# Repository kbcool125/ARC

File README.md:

# ARC
Code, documentation and other items relavent to the Aberystwyth Robotics Club

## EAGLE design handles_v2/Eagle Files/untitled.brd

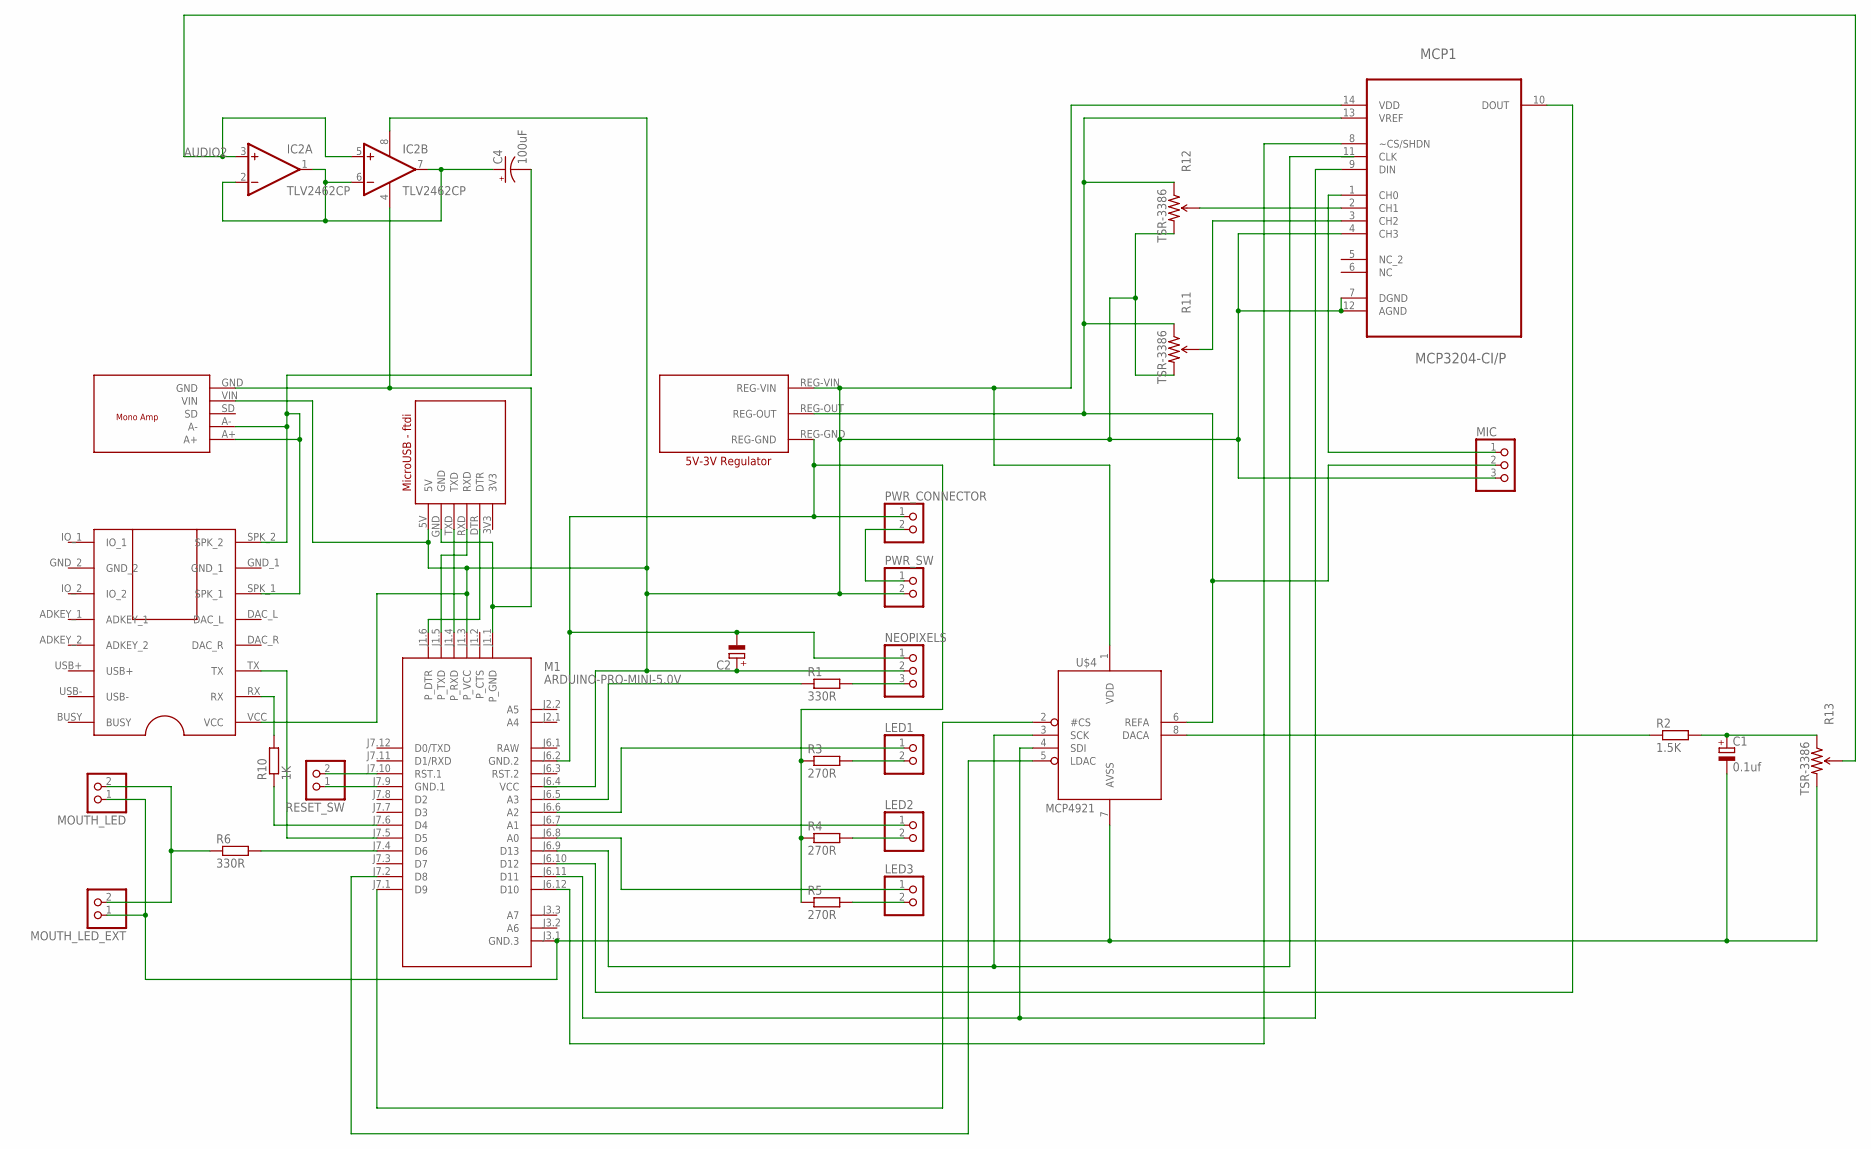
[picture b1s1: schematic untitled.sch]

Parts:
C1: 0.1uf; E2,5-6E
C2: CPOL-EUE2,5-6E; E2,5-6E
C4: 100uF; CPOL-RADIAL-100UF-25V
IC2: TLV2462CP; DIL08
LED1, LED2, LED3: PINHD-1X2; 1X02
M1: ARDUINO-PRO-MINI-5.0V; ARDUINO-PRO-MINI
MCP1: MCP3204-CI/P; DIP254P762X432-14
MIC: PINHD-1X3; 1X03
MOUTH_LED: PINHD-1X2; 1X02
MOUTH_LED_EXT: PINHD-1X2; 1X02
NEOPIXELS: PINHD-1X3; 1X03
PWR_CONNECTOR: PINHD-1X2; 1X02
PWR_SW: PINHD-1X2; 1X02
R1, R6: 330R; 0207/7
R2: 1.5K; 0207/7
R3, R4, R5: 270R; 0207/7
R10: 1K; 0207/7
R11, R12, R13: TSR-3386; 3386U
RESET_SW: PINHD-1X2; 1X02
U$1: DPLAYER-MINI-DEV; DPLAYER-MINI-PAC
U$2: MICRO-USB-DEV; MICRO-USB-PAC
U$4: MCP4921; DIL08
U$5: 5V-TO-3V-REG-DEV; 5V-TO-3V-REG-PAC
U$6: MONO-AMP-DEV; MONO-AMP-PAC

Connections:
3V3: U$2.3V3
AUDIO2: IC2.3 (+IN), IC2.5 (+IN), R13.2 (WIPER)
AVSS: C1.-, M1.J3.1 (GND.3), MOUTH_LED.1, MOUTH_LED_EXT.1, R13.3 (CW), U$4.7 (AVSS)
GND_1: IC2.4 (V-), M1.J1.1 (P_GND), U$1.GND_1, U$2.GND, U$6.GND
GND_2: U$1.GND_2
unnamed: NEOPIXELS.3, R1.2
unnamed: M1.J1.4 (P_RXD), U$2.TXD
unnamed: M1.J1.5 (P_TXD), U$2.RXD
unnamed: M1.J1.6 (P_DTR), U$2.DTR
unnamed: LED3.1, M1.J6.8 (A0)
unnamed: LED1.2, R3.2
unnamed: LED2.2, R4.2
unnamed: C4.2 (-), U$1.SPK_1, U$1.SPK_2, U$6.A+, U$6.A-
unnamed: LED1.1, M1.J6.6 (A2)
unnamed: MCP1.2 (CH1), R12.2 (WIPER)
unnamed: PWR_CONNECTOR.2, PWR_SW.1
unnamed: M1.J7.5 (D5), U$1.TX
unnamed: LED2.1, M1.J6.7 (A1)
unnamed: R10.2, U$1.RX
unnamed: LED3.2, R5.2
unnamed: M1.J7.6 (D4), R10.1
unnamed: C2.-, M1.J6.2 (GND.2), NEOPIXELS.1, PWR_CONNECTOR.1, R3.1, R4.1, R5.1, U$5.REG-GND
unnamed: MCP1.13 (VREF), MIC.2, R11.1 (CCW), R12.1 (CCW), U$4.6 (REFA), U$5.REG-OUT
unnamed: M1.J6.5 (A3), R1.1
unnamed: M1.J7.10 (RST.1), RESET_SW.2
unnamed: M1.J7.9 (GND.1), RESET_SW.1
unnamed: C4.1 (+), IC2.1 (OUT), IC2.2 (-IN), IC2.6 (-IN), IC2.7 (OUT)
unnamed: MCP1.3 (CH2), R11.2 (WIPER)
unnamed: M1.J6.9 (D13), U$4.3 (SCK)
unnamed: M1.J6.10 (D12), MCP1.10 (DOUT)
unnamed: M1.J6.12 (D10), MCP1.8 (~CS/SHDN)
unnamed: M1.J6.11 (D11), MCP1.9 (DIN), U$4.4 (SDI)
unnamed: MCP1.1 (CH0), MIC.1
unnamed: C1.+, R2.2, R13.1 (CCW)
unnamed: M1.J7.4 (D6), R6.2
unnamed: R2.1, U$4.8 (DACA)
unnamed: MOUTH_LED.2, MOUTH_LED_EXT.2, R6.1
unnamed: M1.J7.1 (D9), U$4.2 (#CS)
unnamed: M1.J7.2 (D8), U$4.5 (LDAC)
RAW: M1.J6.1 (RAW)
VCC: M1.J6.4 (VCC)
VDD: C2.+, IC2.8 (V+), M1.J1.3 (P_VCC), MCP1.4 (CH3), MCP1.7 (DGND), MCP1.12 (AGND), MCP1.14 (VDD), MIC.3, NEOPIXELS.2, PWR_SW.2, R11.3 (CW), R12.3 (CW), U$1.VCC, U$2.5V, U$4.1 (VDD), U$5.REG-VIN, U$6.VIN

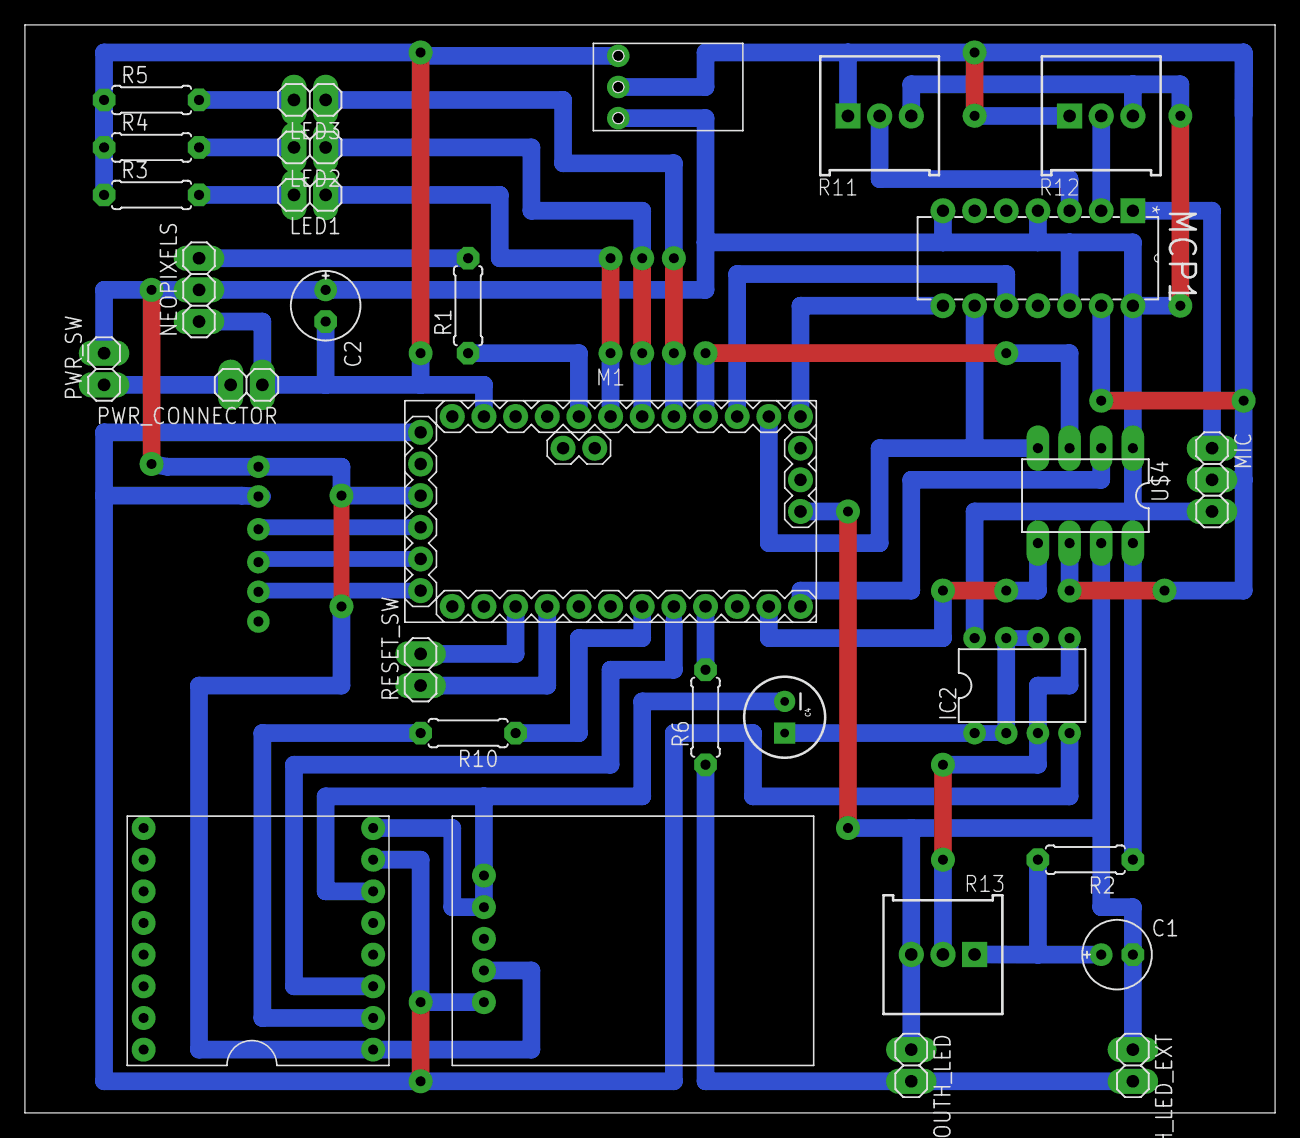
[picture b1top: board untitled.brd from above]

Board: 2 copper layers, 100.3 x 87.3 mm, 31 parts (1 on the bottom side), 38 nets.

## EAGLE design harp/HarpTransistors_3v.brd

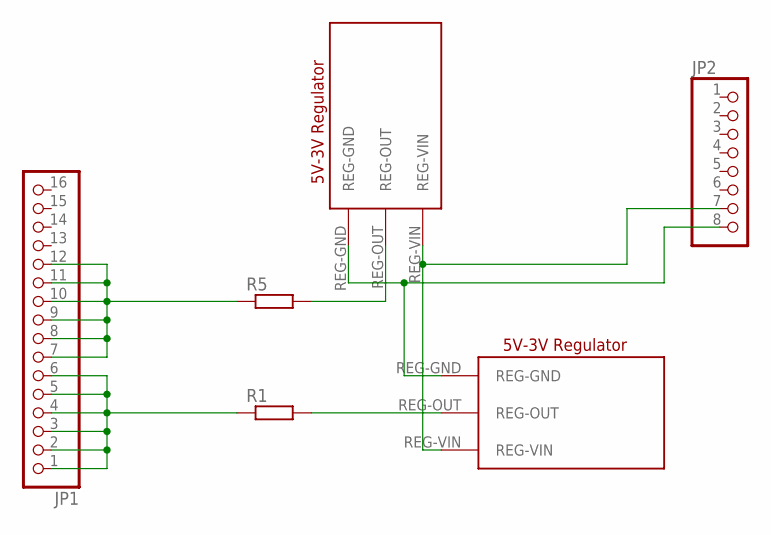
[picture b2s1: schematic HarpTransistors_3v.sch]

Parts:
JP1: PINHD-1X16; 1X16
JP2: PINHD-1X8; 1X08
R1, R5: R-EU_0204/5; 0204/5
U$1, U$2: 5V-TO-3V-REG-DEV; 5V-TO-3V-REG-PAC

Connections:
unnamed: R5.2, U$1.REG-OUT
unnamed: JP1.1, JP1.2, JP1.3, JP1.4, JP1.5, JP1.6, R1.1
unnamed: R1.2, U$2.REG-OUT
unnamed: JP2.8, U$1.REG-GND, U$2.REG-GND
unnamed: JP2.7, U$1.REG-VIN, U$2.REG-VIN
unnamed: JP1.7, JP1.8, JP1.9, JP1.10, JP1.11, JP1.12, R5.1

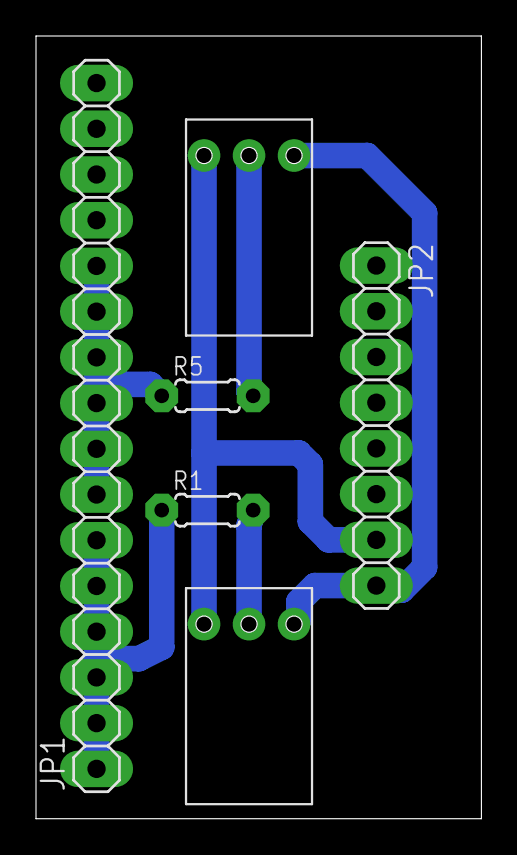
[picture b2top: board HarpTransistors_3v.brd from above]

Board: 2 copper layers, 24.7 x 43.5 mm, 6 parts (0 on the bottom side), 6 nets.

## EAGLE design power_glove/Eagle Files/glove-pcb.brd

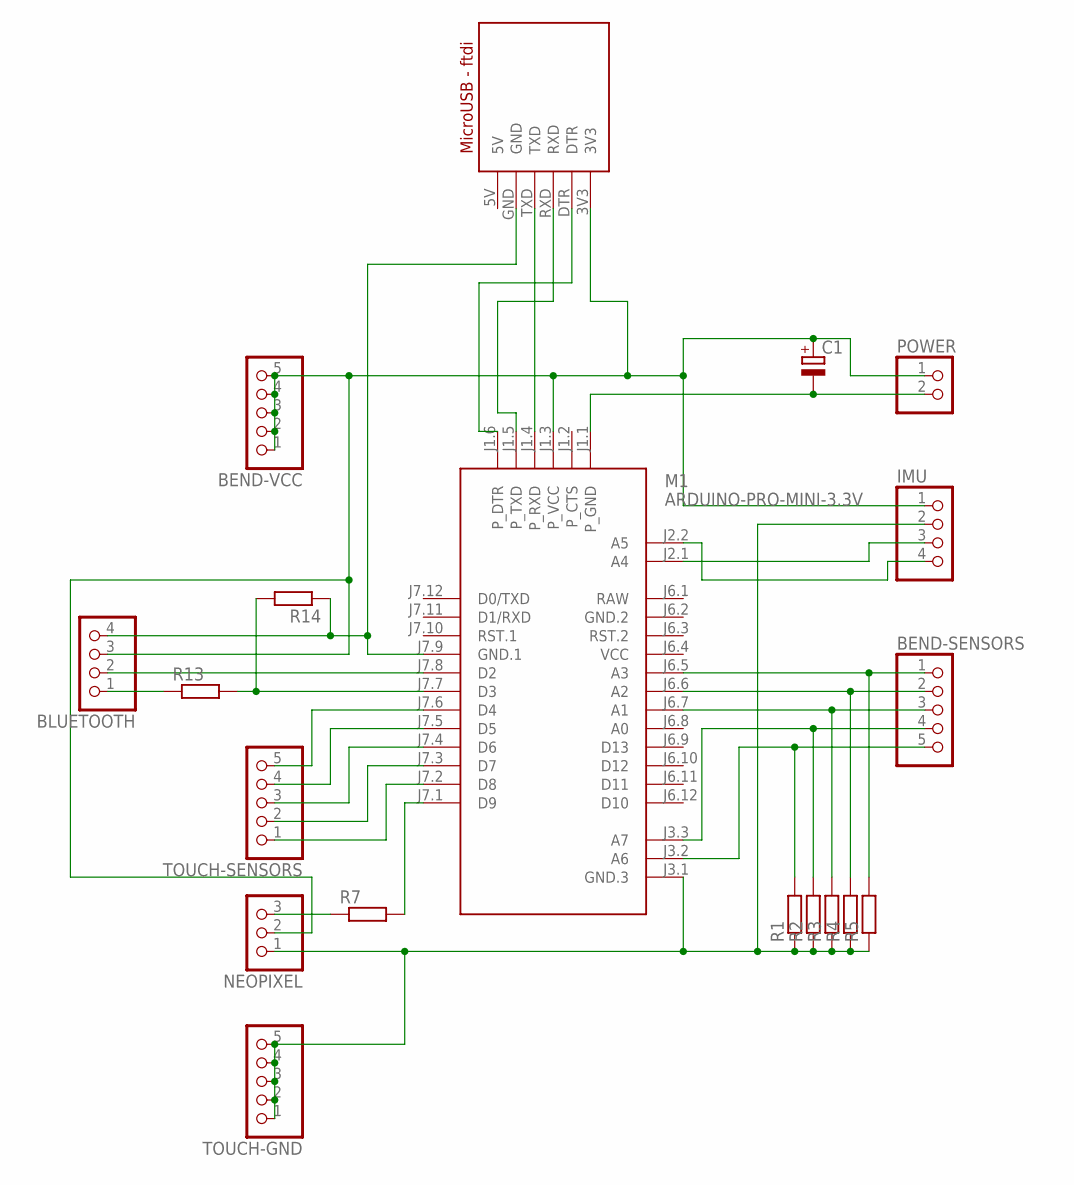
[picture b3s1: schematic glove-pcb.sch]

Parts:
BEND-SENSORS: PINHD-1X5; 1X05
BEND-VCC: PINHD-1X5; 1X05
BLUETOOTH: PINHD-1X4; 1X04
C1: CPOL-EUE2-5; E2-5
IMU: PINHD-1X4; 1X04
M1: ARDUINO-PRO-MINI-3.3V; ARDUINO-PRO-MINI
NEOPIXEL: PINHD-1X3; 1X03
POWER: PINHD-1X2; 1X02
R1, R2, R3, R4, R5: R-EU_0204/7; 0204/7
R7, R13, R14: R-EU_0204/2V; 0204V
TOUCH-GND: PINHD-1X5; 1X05
TOUCH-SENSORS: PINHD-1X5; 1X05
U$1: MICRO-USB-DEV; MICRO-USB-PAC

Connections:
5V: U$1.5V
GND.2: M1.J6.2 (GND.2)
unnamed: NEOPIXEL.3, R7.1
unnamed: IMU.3, M1.J2.1 (A4)
unnamed: M1.J7.1 (D9), R7.2
unnamed: IMU.4, M1.J2.2 (A5)
unnamed: M1.J1.4 (P_RXD), U$1.TXD
unnamed: M1.J1.5 (P_TXD), U$1.RXD
unnamed: BLUETOOTH.1, R13.1
unnamed: BLUETOOTH.2, M1.J7.8 (D2)
unnamed: BEND-SENSORS.1, M1.J6.5 (A3), R5.2
unnamed: BLUETOOTH.4, M1.J7.9 (GND.1), R14.1, U$1.GND
unnamed: IMU.2, M1.J3.1 (GND.3), NEOPIXEL.1, R1.1, R2.1, R3.1, R4.1, R5.1, TOUCH-GND.1, TOUCH-GND.2, TOUCH-GND.3, TOUCH-GND.4, TOUCH-GND.5
unnamed: M1.J7.2 (D8), TOUCH-SENSORS.1
unnamed: M1.J7.3 (D7), TOUCH-SENSORS.2
unnamed: C1.-, M1.J1.1 (P_GND), POWER.2
unnamed: M1.J7.4 (D6), TOUCH-SENSORS.3
unnamed: M1.J7.5 (D5), TOUCH-SENSORS.4
unnamed: M1.J7.6 (D4), TOUCH-SENSORS.5
unnamed: BEND-SENSORS.2, M1.J6.6 (A2), R4.2
unnamed: BEND-SENSORS.3, M1.J6.7 (A1), R3.2
unnamed: BEND-SENSORS.4, M1.J3.3 (A7), R2.2
unnamed: BEND-SENSORS.5, M1.J3.2 (A6), R1.2
unnamed: M1.J7.7 (D3), R13.2, R14.2
unnamed: M1.J1.6 (P_DTR), U$1.DTR
unnamed: BEND-VCC.1, BEND-VCC.2, BEND-VCC.3, BEND-VCC.4, BEND-VCC.5, BLUETOOTH.3, C1.+, IMU.1, M1.J1.3 (P_VCC), NEOPIXEL.2, POWER.1, U$1.3V3
RAW: M1.J6.1 (RAW)
VCC: M1.J6.4 (VCC)

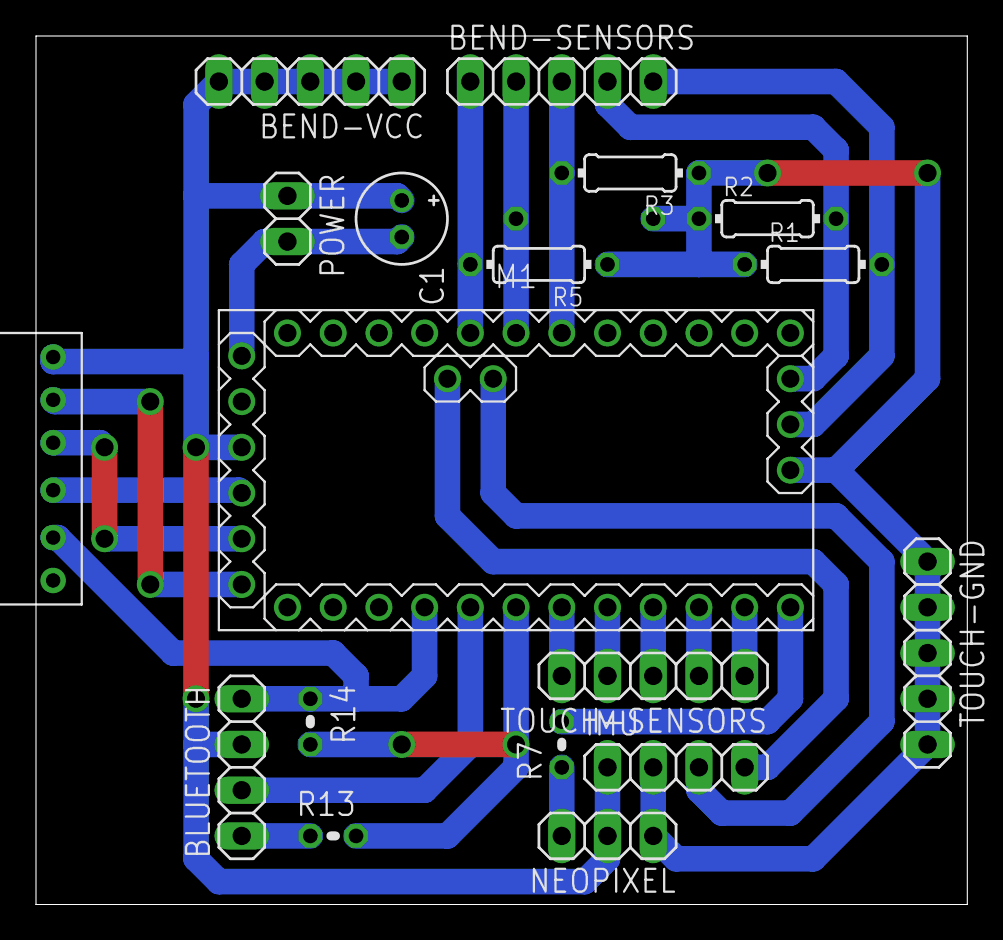
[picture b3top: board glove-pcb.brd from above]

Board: 2 copper layers, 51.7 x 48.2 mm, 19 parts (1 on the bottom side), 24 nets.

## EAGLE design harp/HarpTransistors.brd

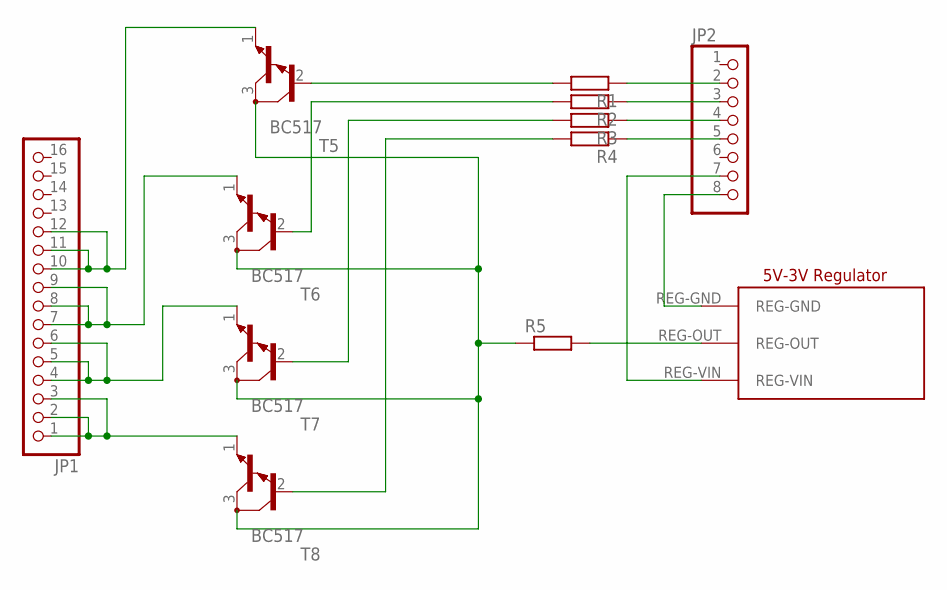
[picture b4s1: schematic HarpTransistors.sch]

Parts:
JP1: PINHD-1X16; 1X16
JP2: PINHD-1X8; 1X08
R1, R2, R3, R4, R5: R-EU_0204/5; 0204/5
T5, T6, T7, T8: BC517; TO92
U$1: 5V-TO-3V-REG-DEV; 5V-TO-3V-REG-PAC

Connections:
unnamed: R1.2, T5.2 (B)
unnamed: JP2.5, R4.1
unnamed: JP2.4, R3.1
unnamed: JP2.3, R2.1
unnamed: JP2.2, R1.1
unnamed: R4.2, T8.2 (B)
unnamed: R2.2, T6.2 (B)
unnamed: JP2.8, U$1.REG-GND
unnamed: JP1.4, JP1.5, JP1.6, T7.1 (E)
unnamed: JP1.7, JP1.8, JP1.9, T6.1 (E)
unnamed: JP1.10, JP1.11, JP1.12, T5.1 (E)
unnamed: R5.1, T5.3 (C), T6.3 (C), T7.3 (C), T8.3 (C)
unnamed: JP1.1, JP1.2, JP1.3, T8.1 (E)
unnamed: R3.2, T7.2 (B)
unnamed: JP2.7, U$1.REG-VIN
unnamed: R5.2, U$1.REG-OUT

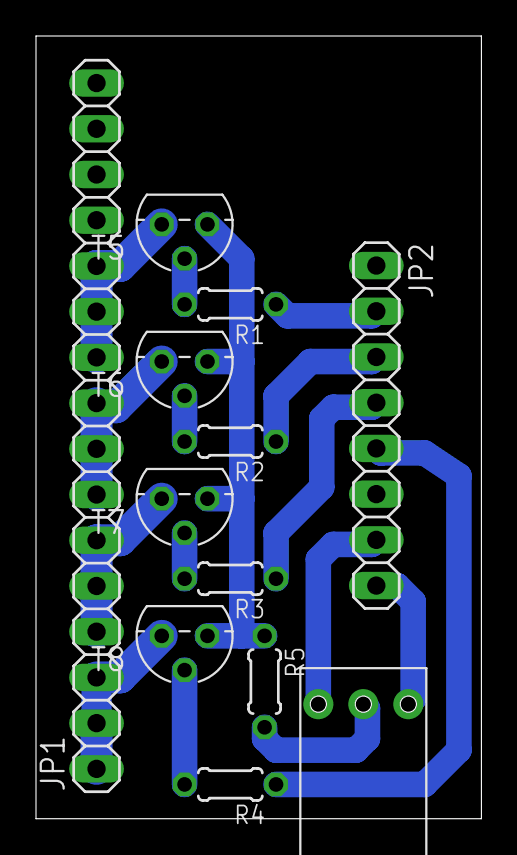
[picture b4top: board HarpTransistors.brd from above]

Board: 2 copper layers, 24.7 x 43.5 mm, 12 parts (0 on the bottom side), 16 nets.

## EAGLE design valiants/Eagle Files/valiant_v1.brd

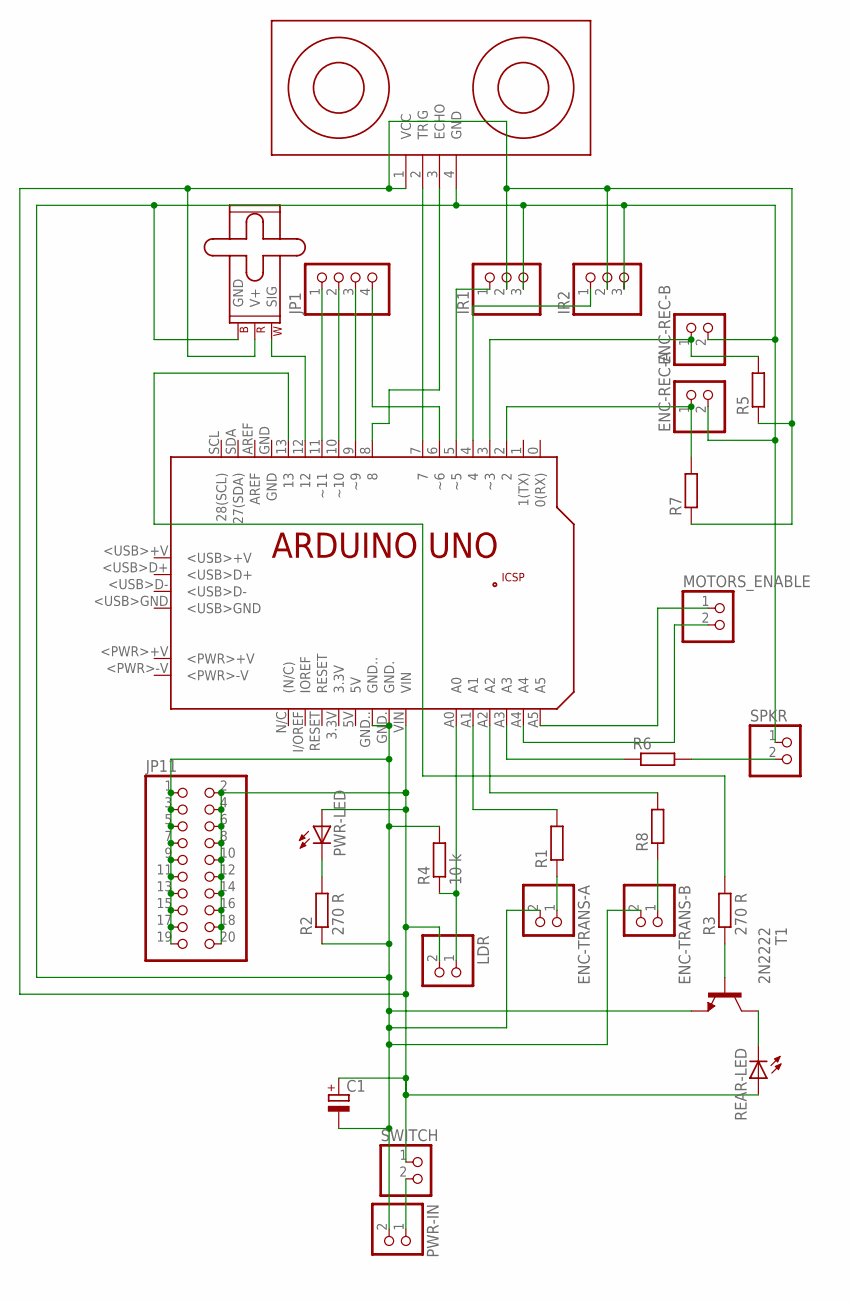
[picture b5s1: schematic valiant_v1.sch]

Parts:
C1: CPOL-EUE2,5-6E; E2,5-6E
ENC-REC-A: PINHD-1X2; 1X02
ENC-REC-B: PINHD-1X2; 1X02
ENC-TRANS-A: PINHD-1X2; 1X02
ENC-TRANS-B: PINHD-1X2; 1X02
IR1, IR2: PINHD-1X3; 1X03
JP1: PINHD-1X4; 1X04
JP11: PINHD-2X10; 2X10
LDR: PINHD-1X2; 1X02
M1: SMALL_SERVO; 1X03
MOTORS_ENABLE: PINHD-1X2; 1X02
PCB1: ARDUINO_UNO
PWR-IN: PINHD-1X2; 1X02
PWR-LED: LED5MM
R1, R5, R6, R7, R8: R-EU_0204/7; 0204/7
R2, R3: 270 R; 0204/7
R4: 10 k; 0204/7
REAR-LED: LED5MM
SPKR: PINHD-1X2; 1X02
SWITCH: PINHD-1X2; 1X02
T1: 2N2222; TO92-EBC-OVAL
U$1: ULTRASONIC-HC-SR04#V

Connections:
unnamed: R3.1, T1.B
unnamed: PCB1.7, U$1.2 (TRIG)
unnamed: JP1.4, PCB1.6 (~6)
unnamed: JP1.3, PCB1.9 (~9)
unnamed: JP1.2, PCB1.10 (~10)
unnamed: JP1.1, PCB1.11 (~11)
unnamed: PCB1.8, U$1.3 (ECHO)
unnamed: ENC-TRANS-A.1, R1.1
unnamed: LDR.1, PCB1.A0, R4.1
unnamed: PCB1.A1, R1.2
unnamed: PCB1.A2, R8.2
unnamed: PCB1.13, R3.2
unnamed: ENC-REC-A.1, PCB1.2, R7.2
unnamed: C1.+, IR1.2, IR2.2, JP11.2, JP11.4, JP11.6, JP11.8, JP11.10, JP11.12, JP11.14, JP11.16, JP11.18, JP11.20, LDR.2, M1.2 (V+), PCB1.VIN, PWR-LED.A, R5.1, R7.1, REAR-LED.A, SWITCH.1, U$1.1 (VCC)
unnamed: PWR-IN.1, SWITCH.2
unnamed: ENC-TRANS-B.1, R8.1
unnamed: PWR-LED.K (C), R2.2
unnamed: M1.1 (SIG), PCB1.12
unnamed: REAR-LED.K (C), T1.C
unnamed: MOTORS_ENABLE.2, PCB1.A4
unnamed: IR1.1, PCB1.5 (~5)
unnamed: IR2.1, PCB1.4
unnamed: ENC-REC-B.1, PCB1.3 (~3), R5.2
unnamed: R6.2, SPKR.2
unnamed: PCB1.A3, R6.1
unnamed: C1.-, ENC-REC-A.2, ENC-REC-B.2, ENC-TRANS-A.2, ENC-TRANS-B.2, IR1.3, IR2.3, JP11.1, JP11.3, JP11.5, JP11.7, JP11.9, JP11.11, JP11.13, JP11.15, JP11.17, JP11.19, M1.3 (GND), PCB1.GND., PCB1.GND.., PWR-IN.2, R2.1, R4.2, SPKR.1, T1.E, U$1.4 (GND)
unnamed: MOTORS_ENABLE.1, PCB1.A5

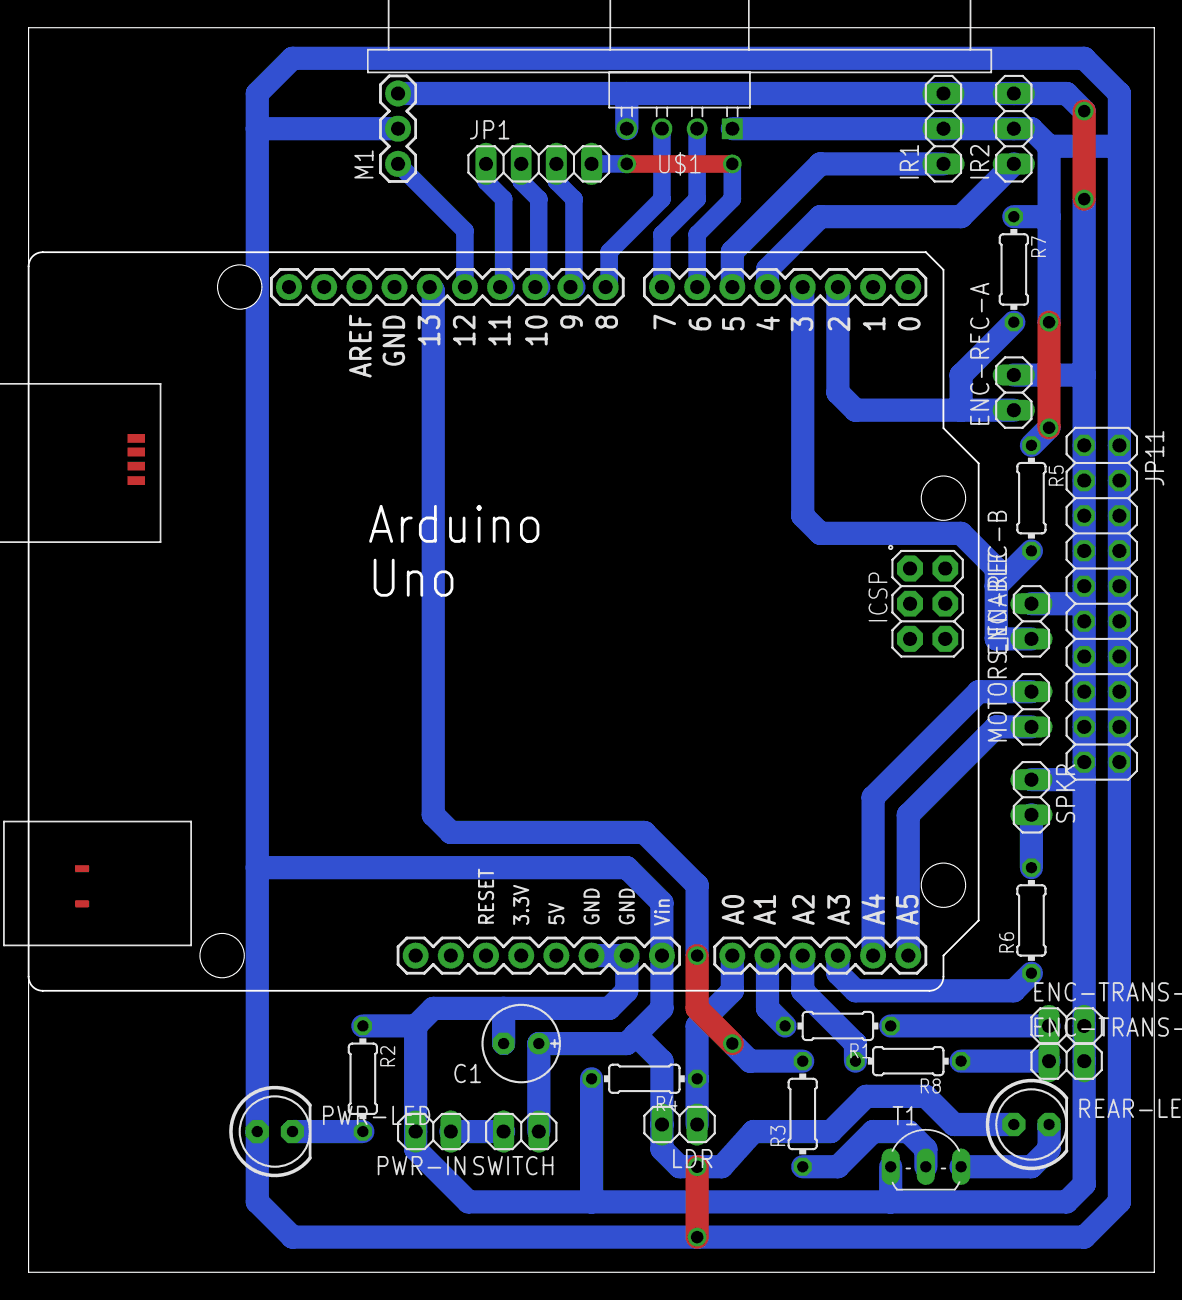
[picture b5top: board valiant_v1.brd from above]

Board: 2 copper layers, 81.3 x 89.8 mm, 28 parts (0 on the bottom side), 27 nets.

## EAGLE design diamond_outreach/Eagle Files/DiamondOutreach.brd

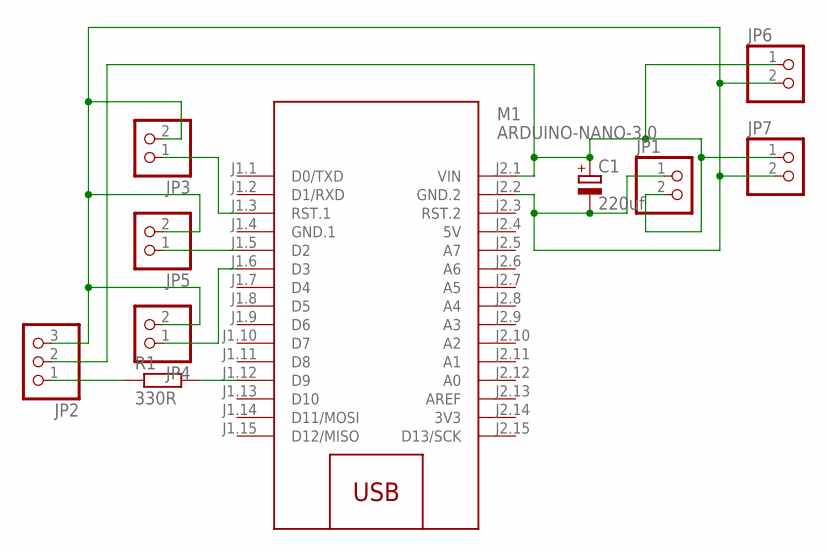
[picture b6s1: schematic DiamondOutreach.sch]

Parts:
C1: 220uf; E2,5-6E
JP1, JP3, JP4, JP5, JP6, JP7: PINHD-1X2; 1X02
JP2: PINHD-1X3; 1X03
M1: ARDUINO-NANO-3.0
R1: 330R; 0204/7

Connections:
3V3: M1.J2.14 (3V3)
5V: M1.J2.4 (5V)
GND.1: M1.J1.4 (GND.1)
unnamed: M1.J1.12 (D9), R1.2
unnamed: JP2.1, R1.1
unnamed: JP3.1, M1.J1.3 (RST.1)
unnamed: C1.+, JP1.2, JP2.2, JP6.1, JP7.1, M1.J2.1 (VIN)
unnamed: JP4.1, M1.J1.6 (D3)
unnamed: JP5.1, M1.J1.5 (D2)
unnamed: C1.-, JP1.1, JP2.3, JP3.2, JP4.2, JP5.2, JP6.2, JP7.2, M1.J2.2 (GND.2)

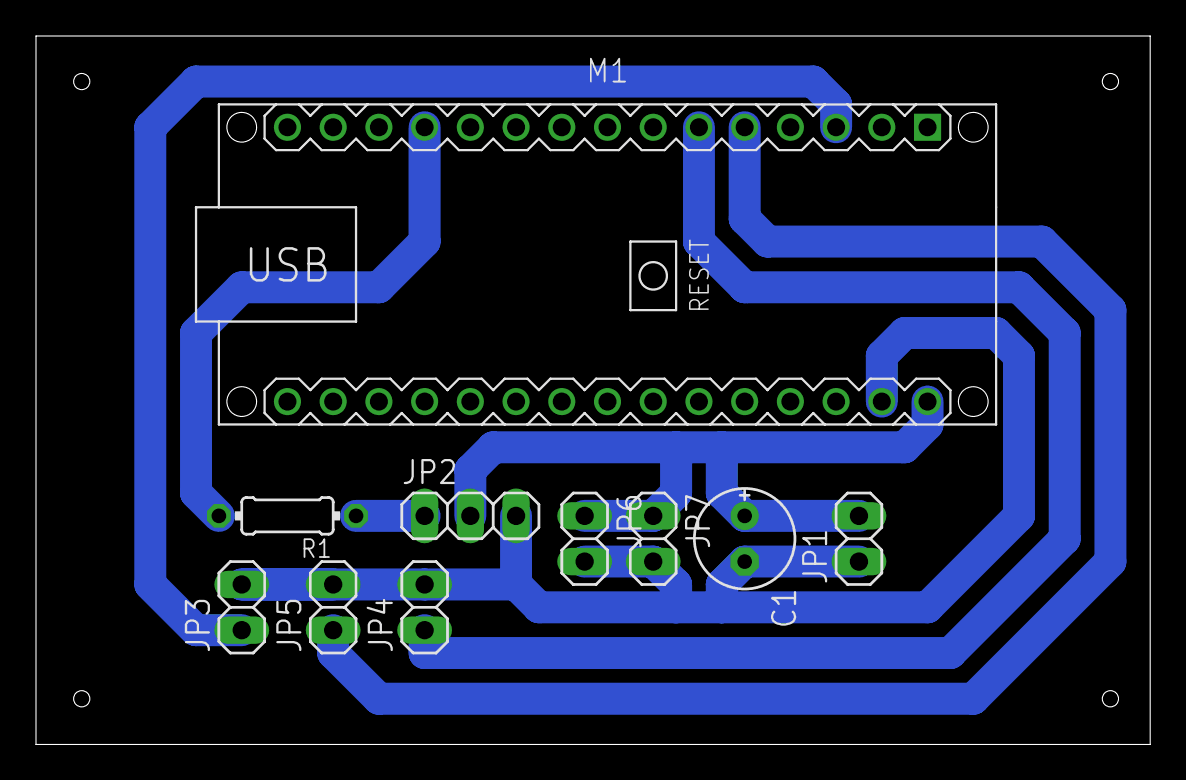
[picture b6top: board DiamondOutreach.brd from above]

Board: 2 copper layers, 61.9 x 39.4 mm, 10 parts (0 on the bottom side), 7 nets.

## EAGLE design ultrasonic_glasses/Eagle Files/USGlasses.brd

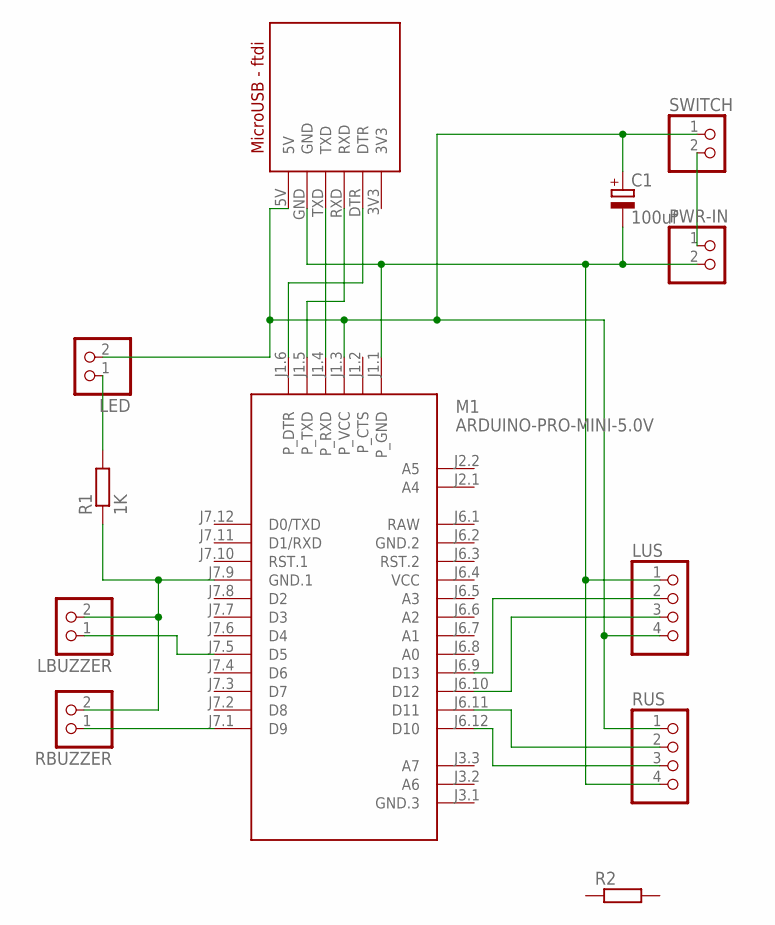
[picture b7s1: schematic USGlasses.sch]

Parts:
C1: 100uf; E2,5-6E
LBUZZER: PINHD-1X2; 1X02
LED: PINHD-1X2; 1X02
LUS: PINHD-1X4; 1X04
M1: ARDUINO-PRO-MINI-5.0V; ARDUINO-PRO-MINI
PWR-IN: PINHD-1X2; 1X02
R1: 1K; 0204/7
R2: R-EU_0204/7; 0204/7
RBUZZER: PINHD-1X2; 1X02
RUS: PINHD-1X4; 1X04
SWITCH: PINHD-1X2; 1X02
U$1: MICRO-USB-DEV; MICRO-USB-PAC

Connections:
3V3: U$1.3V3
GND.2: M1.J6.2 (GND.2)
unnamed: M1.J1.4 (P_RXD), U$1.TXD
unnamed: M1.J1.5 (P_TXD), U$1.RXD
unnamed: M1.J1.6 (P_DTR), U$1.DTR
unnamed: LED.1, R1.2
unnamed: LUS.3, M1.J6.10 (D12)
unnamed: PWR-IN.1, SWITCH.2
unnamed: C1.+, LED.2, LUS.4, M1.J1.3 (P_VCC), RUS.1, SWITCH.1, U$1.5V
unnamed: C1.-, LUS.1, M1.J1.1 (P_GND), PWR-IN.2, RUS.4, U$1.GND
unnamed: LUS.2, M1.J6.9 (D13)
unnamed: M1.J6.11 (D11), RUS.2
unnamed: M1.J6.12 (D10), RUS.3
unnamed: LBUZZER.2, M1.J7.9 (GND.1), R1.1, RBUZZER.2
unnamed: M1.J7.1 (D9), RBUZZER.1
unnamed: LBUZZER.1, M1.J7.5 (D5)
RAW: M1.J6.1 (RAW)
VCC: M1.J6.4 (VCC)

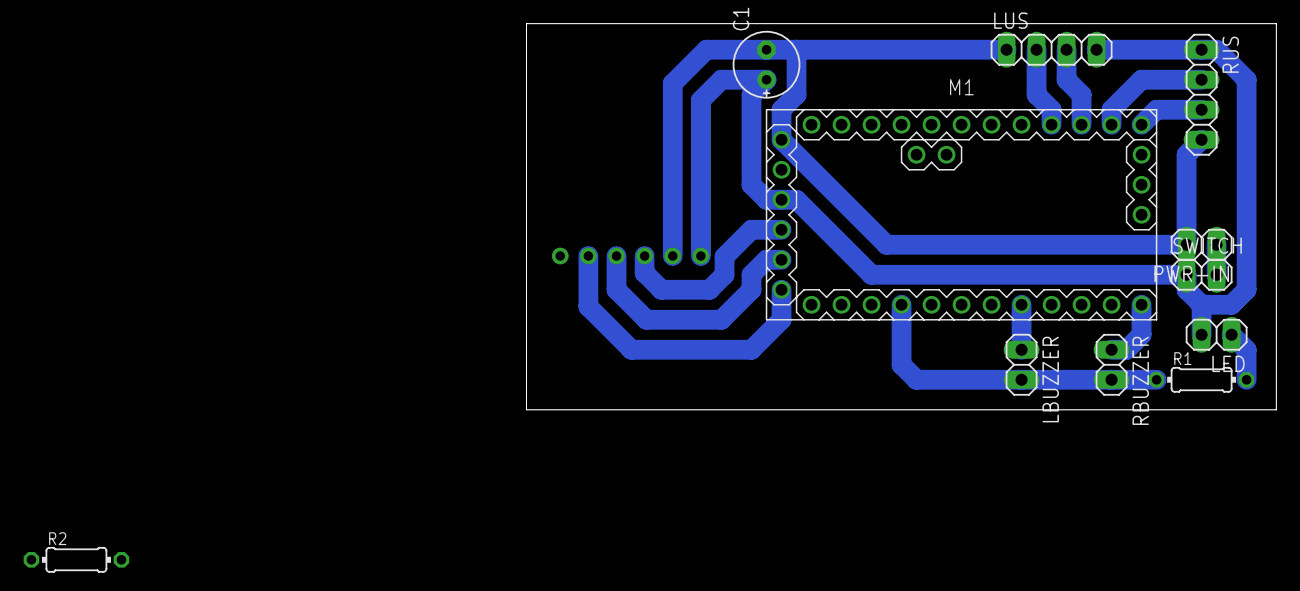
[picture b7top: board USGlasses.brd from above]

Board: 2 copper layers, 63.5 x 32.7 mm, 12 parts (1 on the bottom side), 14 nets.

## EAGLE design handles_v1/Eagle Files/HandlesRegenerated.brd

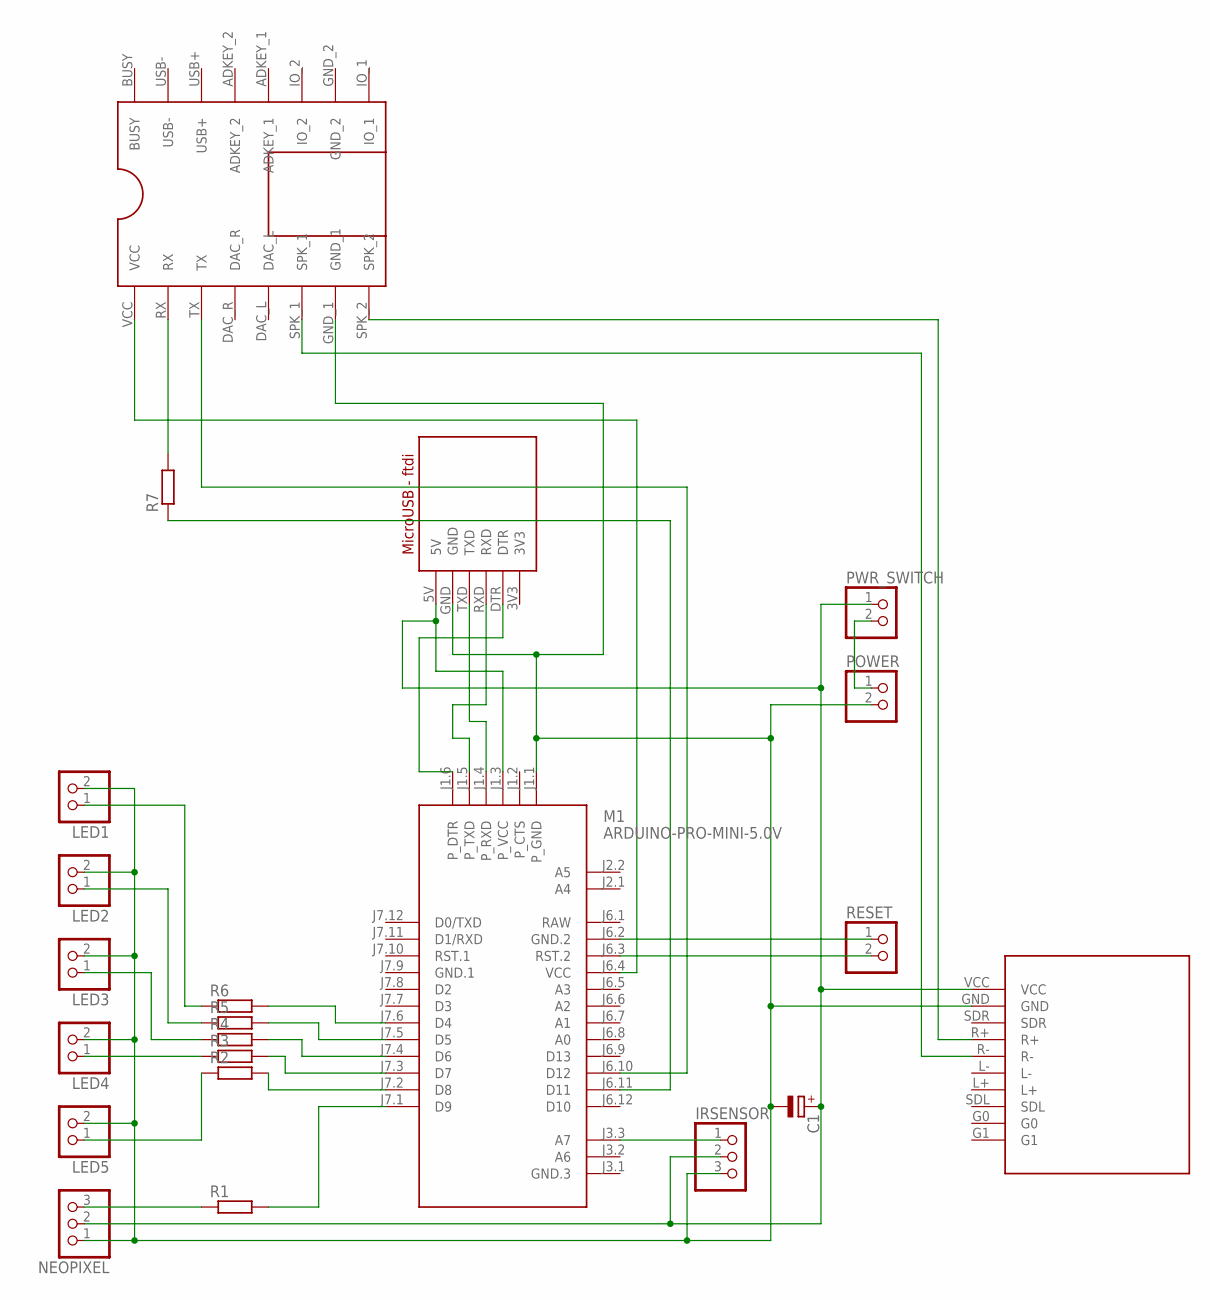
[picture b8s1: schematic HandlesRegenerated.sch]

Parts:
C1: CPOL-EUE2,5-6E; E2,5-6E
IRSENSOR: PINHD-1X3; 1X03
LED1, LED2, LED3, LED4, LED5: PINHD-1X2; 1X02
M1: ARDUINO-PRO-MINI-5.0V; ARDUINO-PRO-MINI
NEOPIXEL: PINHD-1X3; 1X03
POWER: PINHD-1X2; 1X02
PWR_SWITCH: PINHD-1X2; 1X02
R1, R2, R3, R4, R5, R6: R-EU_0204/7; 0204/7
R7: R-EU_0207/7; 0207/7
RESET: PINHD-1X2; 1X02
U$1: MICRO-USB-DEV; MICRO-USB-PAC
U$2: STEREO-AUDIO-AMP-DEV; STEREO-AUDIO-AMP-PAC
U$3: DPLAYER-MINI-DEV; DPLAYER-MINI-PAC

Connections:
3V3: U$1.3V3
G0: U$2.G0
G1: U$2.G1
GND.1: M1.J7.9 (GND.1)
GND_2: U$3.GND_2
unnamed: M1.J7.1 (D9), R1.2
unnamed: NEOPIXEL.3, R1.1
unnamed: POWER.1, PWR_SWITCH.2
unnamed: U$2.R+, U$3.SPK_2
unnamed: M1.J1.4 (P_RXD), U$1.TXD
unnamed: M1.J1.5 (P_TXD), U$1.RXD
unnamed: M1.J7.2 (D8), R2.2
unnamed: M1.J7.3 (D7), R3.2
unnamed: M1.J7.4 (D6), R4.2
unnamed: M1.J7.5 (D5), R5.2
unnamed: M1.J7.6 (D4), R6.2
unnamed: LED5.1, R2.1
unnamed: LED1.1, R6.1
unnamed: LED2.1, R5.1
unnamed: LED3.1, R4.1
unnamed: LED4.1, R3.1
unnamed: C1.-, IRSENSOR.3, LED1.2, LED2.2, LED3.2, LED4.2, LED5.2, M1.J1.1 (P_GND), NEOPIXEL.1, POWER.2, U$1.GND, U$2.GND, U$3.GND_1
unnamed: M1.J6.4 (VCC), U$3.VCC
unnamed: M1.J6.2 (GND.2), RESET.1
unnamed: M1.J6.3 (RST.2), RESET.2
unnamed: U$2.R-, U$3.SPK_1
unnamed: R7.2, U$3.RX
unnamed: M1.J6.11 (D11), R7.1
unnamed: M1.J6.10 (D12), U$3.TX
unnamed: IRSENSOR.1, M1.J3.3 (A7)
unnamed: M1.J1.6 (P_DTR), U$1.DTR
unnamed: C1.+, IRSENSOR.2, M1.J1.3 (P_VCC), NEOPIXEL.2, PWR_SWITCH.1, U$1.5V, U$2.VCC
RAW: M1.J6.1 (RAW)

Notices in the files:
parts and their libraries:
diy-modules: Released under the Creative Commons Attribution 4.0 International License: http://creativecommons.org/licenses/by/4.0
SparkFun-Capacitors: Licensing: Creative Commons ShareAlike 4.0 International - https://creativecommons.org/licenses/by-sa/4.0
